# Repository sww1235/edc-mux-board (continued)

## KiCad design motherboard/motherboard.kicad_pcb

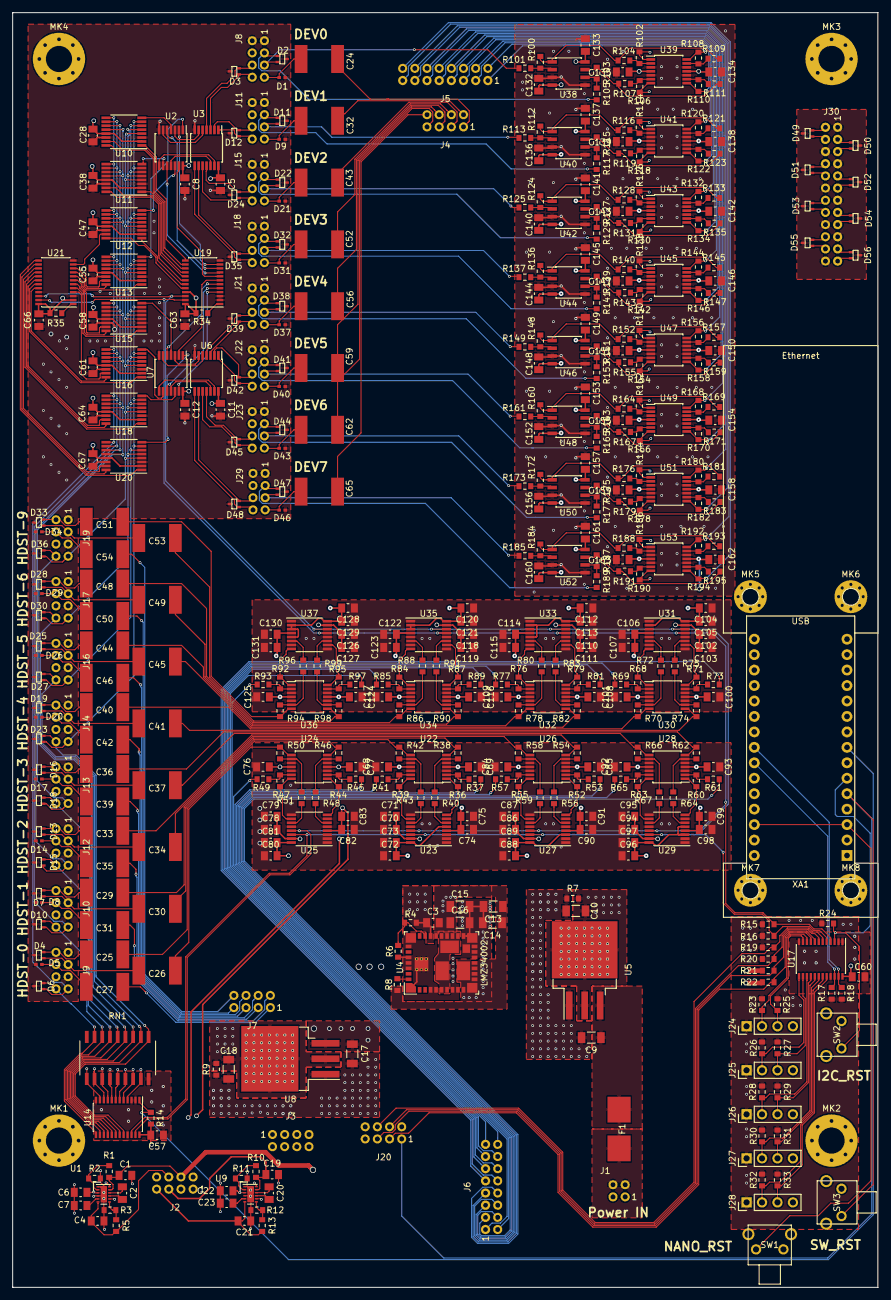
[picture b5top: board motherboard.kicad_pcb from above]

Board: 4 copper layers, 142.2 x 209.6 mm, 511 parts (0 on the bottom side), 384 nets.

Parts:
C1, C4, C19, C21: 2u2F; C_0805_2012Metric_Pad1.15x1.50mm_HandSolder
C2, C20: 0.47uF; C_0805_2012Metric_Pad1.15x1.50mm_HandSolder
C3: 15uF; C_0805_2012Metric_Pad1.15x1.50mm_HandSolder
C5, C8, C11, C12, C28, C38, C47, C55, C57, C58, C60, C61, C63, C64, C66, C67, C68, C69, C71, C72, C75, C76, C77, C79, C80, C83, C84, C85, C87, C88, C91, C92, C93, C95, C96, C99, C100, C101, C103, C104, C107, C108, C109, C111, C112, C115, C116, C117, C119, C120, C123, C124, C125, C127, C128, C131, C132, C133, C134, C135, C136, C137, C138, C139, C140, C141, C142, C143, C144, C145, C146, C147, C148, C149, C150, C151, C152, C153, C154, C155, C156, C157, C158, C159, C160, C161, C162, C163: 0.1uF; C_0805_2012Metric_Pad1.15x1.50mm_HandSolder
C6, C7, C22, C23: 4u7F; C_0805_2012Metric_Pad1.15x1.50mm_HandSolder
C9, C10, C17, C18: 10uF; C_1206_3216Metric_Pad1.24x1.80mm_HandSolder
C13, C14, C15, C16: 22uF; C_1206_3216Metric_Pad1.24x1.80mm_HandSolder
C24, C25, C26, C27, C29, C30, C31, C32, C33, C34, C35, C36, C37, C39, C40, C41, C42, C43, C44, C45, C46, C48, C49, C50, C51, C52, C53, C54, C56, C59, C62, C65: 1uF; Kemet_CAP_2220_5750Metric_D
C70, C73, C74, C78, C81, C82, C86, C89, C90, C94, C97, C98, C102, C105, C106, C110, C113, C114, C118, C121, C122, C126, C129, C130: 0.01uF; C_0805_2012Metric_Pad1.15x1.50mm_HandSolder
D1, D5, D8, D9, D14, D17, D20, D21, D26, D29, D31, D34, D37, D40, D43, D46: TPD1E10B06; DPY_(R-PX1SON-N2)
D2, D3, D4, D6, D7, D10, D11, D12, D13, D15, D16, D18, D19, D22, D23, D24, D25, D27, D28, D30, D32, D33, D35, D36, D38, D39, D41, D42, D44, D45, D47, D48, D49, D50, D51, D52, D53, D54, D55, D56: 0582BQ; SC-75_3L
F1: 5A; NANO-0154-OMNI-BLOK-Fuse-Holder
J1: Power In (Male-top); DF11-4DP-2DSA
J2: Power Out (Male-top); DF11-8DP-2DSA
J3: GND (Male-top); DF11-8DP-2DSA
J4: MIC-IN (Male-top); DF11-8DP-2DSA
J5: Headphone Audio Out (Male-top); DF11-16DP-2DSA
J6: Headphone Audio In (Male-top); DF11-16DP-2DSA
J7: MIC-OUT (Male-top); DF11-8DP-2DSA
J8: Device 0; DF11-8DP-2DSA
J9: Headset 0; DF11-8DP-2DSA
J10: Headset 1; DF11-8DP-2DSA
J11: Device 1; DF11-8DP-2DSA
J12: Headset 2; DF11-8DP-2DSA
J13: Headset 3; DF11-8DP-2DSA
J14: Headset 4; DF11-8DP-2DSA
J15: Device 2; DF11-8DP-2DSA
J16: Headset 5; DF11-8DP-2DSA
J17: Headset 6; DF11-8DP-2DSA
J18: Device 3; DF11-8DP-2DSA
J19: Headset 7; DF11-8DP-2DSA
J20: I2C and RESET (Male-top); DF11-8DP-2DSA
J21: Device 4; DF11-8DP-2DSA
J22: Device 5; DF11-8DP-2DSA
J23: Device 6; DF11-8DP-2DSA
J24: 5V-I2C-2; PinHeader_1x04_P2.54mm_Vertical
J25: 5V-I2C-3; PinHeader_1x04_P2.54mm_Vertical
J26: 5V-I2C-4; PinHeader_1x04_P2.54mm_Vertical
J27: 5V-I2C-5; PinHeader_1x04_P2.54mm_Vertical
J28: 5V-I2C-6; PinHeader_1x04_P2.54mm_Vertical
J29: Device 7; DF11-8DP-2DSA
J30: Output to Mixer; DF11-24DP-2DSA
MK1, MK2, MK3, MK4: Mounting_Hole_PAD; MountingHole_4.3mm_M4_Pad_Via
MK5, MK6, MK7, MK8: Mounting_Hole_PAD; MountingHole_2.7mm_M2.5_Pad_Via
R1, R5: 75kΩ; R_0603_1608Metric_Pad0.84x1.00mm_HandSolder
R2, R3, R11, R12: 68kΩ; R_0603_1608Metric_Pad0.84x1.00mm_HandSolder
R4: 174kΩ; R_0603_1608Metric_Pad0.84x1.00mm_HandSolder
R6: 22.6kΩ; R_0603_1608Metric_Pad0.84x1.00mm_HandSolder
R7, R9: 1.3Ω; R_0603_1608Metric_Pad0.84x1.00mm_HandSolder
R8: 143kΩ; R_0603_1608Metric_Pad0.84x1.00mm_HandSolder
R10, R13: 220kΩ; R_0603_1608Metric_Pad0.84x1.00mm_HandSolder
R14, R24, R34, R35, R40, R43, R48, R51, R56, R59, R64, R67, R72, R75, R80, R83, R88, R91, R96, R99: 10kΩ; R_0603_1608Metric_Pad0.84x1.00mm_HandSolder
R15, R16, R17, R18, R19, R20, R21, R22, R23, R25, R26, R27, R28, R29, R30, R31, R32, R33: 4k7Ω; R_0603_1608Metric_Pad0.84x1.00mm_HandSolder
R36, R37, R38, R39, R41, R42, R44, R45, R46, R47, R49, R50, R52, R53, R54, R55, R57, R58, R60, R61, R62, R63, R65, R66, R68, R69, R70, R71, R73, R74, R76, R77, R78, R79, R81, R82, R84, R85, R86, R87, R89, R90, R92, R93, R94, R95, R97, R98, R100, R101, R102, R103, R104, R105, R106, R107, R108, R109, R110, R111, R112, R113, R114, R115, R116, R117, R118, R119, R120, R121, R122, R123, R124, R125, R126, R127, R128, R129, R130, R131, R132, R133, R134, R135, R136, R137, R138, R139, R140, R141, R142, R143, R144, R145, R146, R147, R148, R149, R150, R151, R152, R153, R154, R155, R156, R157, R158, R159, R160, R161, R162, R163, R164, R165, R166, R167, R168, R169, R170, R171, R172, R173, R174, R175, R176, R177, R178, R179, R180, R181, R182, R183, R184, R185, R186, R187, R188, R189, R190, R191, R192, R193, R194, R195: 100kΩ; R_0603_1608Metric_Pad0.84x1.00mm_HandSolder
RN1: 4818P-T02-202LF; SOM-18
SW1: Nano Reset; TL1105WF
SW2: I2C Reset; TL1105WF
SW3: SPST Reset; TL1105WF
U1, U9: LM27762; WSON-12-1EP_3x2mm_P0.5mm
U2, U7: 74ACT32; TSSOP-14_4.4x5mm_P0.65mm
U3, U6: TS12A44514; TSSOP-14_4.4x5mm_P0.65mm
U4: LMZ34002; RKG_(S-PB1QFN-N41)
U5: LM1085-12V; TO-263-3_TabPin4
U8: LM1085-5V; TO-263-3_TabPin4
U10, U11, U12, U13, U15, U16, U18, U20: ADG708; TSSOP-16_4.4x5mm_P0.65mm
U14, U19, U21: TCA9555; TSSOP-24_4.4x7.8mm_P0.65mm
U17: TCA9548A; TSSOP-24_4.4x7.8mm_P0.65mm
U22, U24, U26, U28, U30, U32, U34, U36, U39, U41, U43, U45, U47, U49, U51, U53: OPA1604; TSSOP-14_4.4x5mm_P0.65mm
U23, U25, U27, U29, U31, U33, U35, U37: DS1882; TSSOP-16_4.4x5mm_P0.65mm
U38, U40, U42, U44, U46, U48, U50, U52: OPA1602; SOIC-8_3.9x4.9mm_P1.27mm
XA1: Nano_Headers; Nano-Header-Ethernet-4NANO

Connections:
+2V5: C1.1, J2.4, R1.1, R21.1, R22.1, U1.11
+3V3: C60.2, U17.24, XA1.17
+5V: C5.1, C6.1, C8.1, C11.1, C12.1, C18.1, C22.1, C28.1, C38.1, C47.1, C55.1, C57.2, C58.1, C61.1, C63.2, C64.1, C66.2, C67.1, C72.2, C73.2, C80.2, C81.2, C88.2, C89.2, C96.2, C97.2, C104.2, C105.2, C112.2, C113.2, C120.2, C121.2, C128.2, C129.2, J2.1, J8.4, J9.6, J10.6, J11.4, J12.6, J13.6, J14.6, J15.4, J16.6, J17.6, J18.4, J19.6, J21.4, J22.4, J23.4, J24.1, J25.1, J26.1, J27.1, J28.1, J29.4, R9.2, R14.1, R15.1, R16.1, R17.1, R18.1, R19.1, R20.1, R23.1, R24.1, R25.1, R26.1, R27.1, R28.1, R29.1, R30.1, R31.1, R32.1, R33.1, R34.1, R35.1, U1.3, U1.8, U1.12, U2.14, U3.14, U6.14, U7.14, U8.2, U8.4, U9.3, U9.8, U9.12, U10.2, U10.13, U11.2, U11.13, U12.2, U12.13, U13.2, U13.13, U14.24, U15.2, U15.13, U16.2, U16.13, U18.2, U18.13, U19.21, U19.24, U20.2, U20.13, U21.2, U21.24, U23.5, U23.16, U25.16, U27.3, U27.16, U29.3, U29.5, U29.16, U31.2, U31.16, U33.2, U33.5, U33.16, U35.2, U35.3, U35.16, U37.2, U37.3, U37.5, U37.16, XA1.27
+5VA: C19.1, C70.2, C71.2, C78.2, C79.2, C86.2, C87.2, C94.2, C95.2, C102.2, C103.2, C110.2, C111.2, C118.2, C119.2, C126.2, C127.2, J2.5, R10.1, U9.11, U23.15, U25.15, U27.15, U29.15, U31.15, U33.15, U35.15, U37.15
+12V: C3.1, C10.1, C17.1, C69.2, C77.2, C85.2, C93.2, C101.2, C109.2, C117.2, C125.2, C133.2, C135.2, C137.2, C139.2, C141.2, C143.2, C145.2, C147.2, C149.2, C151.2, C153.2, C155.2, C157.2, C159.2, C161.2, C163.2, J2.2, R4.1, R7.2, U4.26, U5.2, U5.4, U8.3, U22.4, U24.4, U26.4, U28.4, U30.4, U32.4, U34.4, U36.4, U38.8, U39.4, U40.8, U41.4, U42.8, U43.4, U44.8, U45.4, U46.8, U47.4, U48.8, U49.4, U50.8, U51.4, U52.8, U53.4
-2.5V: C4.2, J2.6, R5.2, U1.6
-5VA: C21.2, C74.2, C75.2, C82.2, C83.2, C90.2, C91.2, C98.2, C99.2, C106.2, C107.2, C114.2, C115.2, C122.2, C123.2, C130.2, C131.2, J2.7, R13.2, U9.6, U23.4, U25.4, U27.4, U29.4, U31.4, U33.4, U35.4, U37.4
-12VA: C13.2, C14.2, C15.2, C16.2, C68.2, C76.2, C84.2, C92.2, C100.2, C108.2, C116.2, C124.2, C132.2, C134.2, C136.2, C138.2, C140.2, C142.2, C144.2, C146.2, C148.2, C150.2, C152.2, C154.2, C156.2, C158.2, C160.2, C162.2, J2.8, R6.2, U4.1, U4.4, U4.5, U4.8, U4.9, U4.16, U4.17, U4.18, U4.19, U4.20, U4.29, U4.30, U4.32, U4.33, U4.34, U4.37, U4.40, U22.11, U24.11, U26.11, U28.11, U30.11, U32.11, U34.11, U36.11, U38.4, U39.11, U40.4, U41.11, U42.4, U43.11, U44.4, U45.11, U46.4, U47.11, U48.4, U49.11, U50.4, U51.11, U52.4, U53.11
/Arduino Nano Header Connections + Ethernet connection/5V-SCL: R17.2, U17.22, XA1.24
/Arduino Nano Header Connections + Ethernet connection/5V-SDA: R18.2, U17.23, XA1.23
/Arduino Nano Header Connections + Ethernet connection/D2_SPST: J20.1, SW3.1, XA1.5
/Arduino Nano Header Connections + Ethernet connection/D3_I2C: R24.2, SW2.1, U17.3, XA1.6
/Arduino Nano Header Connections + Ethernet connection/D5_INT: R14.2, U14.1, XA1.8
/Arduino Nano Header Connections + Ethernet connection/Nano_RST: SW1.1, XA1.3, XA1.28
/Audio Mux and Control/2v5-SCL-0: J20.3, R22.2, U17.9
/Audio Mux and Control/2v5-SDA-0: J20.5, R21.2, U17.8
/Audio Mux and Control/5V-SCL-0: R16.2, U14.22, U17.5, U19.22, U21.22, U23.14, U25.14, U27.14, U29.14, U31.14, U33.14, U35.14, U37.14
/Audio Mux and Control/5V-SCL-1: J20.4, R20.2, U17.7
/Audio Mux and Control/5V-SCL-2: J24.3, R25.2, U17.11
/Audio Mux and Control/5V-SCL-3: J25.3, R27.2, U17.14
/Audio Mux and Control/5V-SCL-4: J26.3, R29.2, U17.16
/Audio Mux and Control/5V-SCL-5: J27.3, R31.2, U17.18
/Audio Mux and Control/5V-SCL-6: J28.3, R33.2, U17.20
/Audio Mux and Control/5V-SDA-0: R15.2, U14.23, U17.4, U19.23, U21.23, U23.13, U25.13, U27.13, U29.13, U31.13, U33.13, U35.13, U37.13
/Audio Mux and Control/5V-SDA-1: J20.6, R19.2, U17.6
/Audio Mux and Control/5V-SDA-2: J24.2, R23.2, U17.10
/Audio Mux and Control/5V-SDA-3: J25.2, R26.2, U17.13
/Audio Mux and Control/5V-SDA-4: J26.2, R28.2, U17.15
/Audio Mux and Control/5V-SDA-5: J27.2, R30.2, U17.17
/Audio Mux and Control/5V-SDA-6: J28.2, R32.2, U17.19
/Audio Mux and Control/DEV-PTT-TRGR-0: U2.6, U3.5
/Audio Mux and Control/DEV-PTT-TRGR-1: U2.8, U3.13
/Audio Mux and Control/DEV-PTT-TRGR-2: U2.11, U3.12
/Audio Mux and Control/DEV-PTT-TRGR-3: U2.3, U3.6
/Audio Mux and Control/DEV-PTT-TRGR-4: U6.5, U7.6
/Audio Mux and Control/DEV-PTT-TRGR-5: U6.13, U7.8
/Audio Mux and Control/DEV-PTT-TRGR-6: U6.12, U7.11
/Audio Mux and Control/DEV-PTT-TRGR-7: U6.6, U7.3
/Audio Mux and Control/DEV-PTT-XBAR-CTL0: U10.1, U19.13
/Audio Mux and Control/DEV-PTT-XBAR-CTL1: U10.16, U19.15
/Audio Mux and Control/DEV-PTT-XBAR-CTL2: U10.15, U19.14
/Audio Mux and Control/DEV-PTT-XBAR-CTL3: U11.1, U19.16
/Audio Mux and Control/DEV-PTT-XBAR-CTL4: U11.16, U19.18
/Audio Mux and Control/DEV-PTT-XBAR-CTL5: U11.15, U19.17
/Audio Mux and Control/DEV-PTT-XBAR-CTL6: U12.1, U19.19
/Audio Mux and Control/DEV-PTT-XBAR-CTL7: U12.16, U19.20
/Audio Mux and Control/DEV-PTT-XBAR-CTL8: U12.15, U21.11
/Audio Mux and Control/DEV-PTT-XBAR-CTL9: U13.1, U21.8
/Audio Mux and Control/DEV-PTT-XBAR-CTL10: U13.16, U21.9
/Audio Mux and Control/DEV-PTT-XBAR-CTL11: U13.15, U21.10
/Audio Mux and Control/DEV-PTT-XBAR-CTL12: U15.1, U21.5
/Audio Mux and Control/DEV-PTT-XBAR-CTL13: U15.16, U21.6
/Audio Mux and Control/DEV-PTT-XBAR-CTL14: U15.15, U21.7
/Audio Mux and Control/DEV-PTT-XBAR-CTL15: U16.1, U21.19
/Audio Mux and Control/DEV-PTT-XBAR-CTL16: U16.16, U21.20
/Audio Mux and Control/DEV-PTT-XBAR-CTL17: U16.15, U21.4
/Audio Mux and Control/DEV-PTT-XBAR-CTL18: U18.1, U21.16
/Audio Mux and Control/DEV-PTT-XBAR-CTL19: U18.16, U21.17
/Audio Mux and Control/DEV-PTT-XBAR-CTL20: U18.15, U21.18
/Audio Mux and Control/DEV-PTT-XBAR-CTL21: U20.1, U21.13
/Audio Mux and Control/DEV-PTT-XBAR-CTL22: U20.16, U21.14
/Audio Mux and Control/DEV-PTT-XBAR-CTL23: U20.15, U21.15
/Audio Mux and Control/Device LR Distro Amplifier 0/L_IN: D2.2, J8.5, R101.2
/Audio Mux and Control/Device LR Distro Amplifier 0/R_IN: D2.1, J8.3, R105.2
/Audio Mux and Control/Device LR Distro Amplifier 1/L_IN: D11.2, J11.5, R113.2
/Audio Mux and Control/Device LR Distro Amplifier 1/R_IN: D11.1, J11.3, R117.2
/Audio Mux and Control/Device LR Distro Amplifier 2/L_IN: D22.2, J15.5, R125.2
/Audio Mux and Control/Device LR Distro Amplifier 2/R_IN: D22.1, J15.3, R129.2
/Audio Mux and Control/Device LR Distro Amplifier 3/L_IN: D32.2, J18.5, R137.2
/Audio Mux and Control/Device LR Distro Amplifier 3/R_IN: D32.1, J18.3, R141.2
/Audio Mux and Control/Device LR Distro Amplifier 4/L_IN: D38.2, J21.5, R149.2
/Audio Mux and Control/Device LR Distro Amplifier 4/R_IN: D38.1, J21.3, R153.2
/Audio Mux and Control/Device LR Distro Amplifier 5/L_IN: D41.2, J22.5, R161.2
/Audio Mux and Control/Device LR Distro Amplifier 5/R_IN: D41.1, J22.3, R165.2
/Audio Mux and Control/Device LR Distro Amplifier 6/L_IN: D44.2, J23.5, R173.2
/Audio Mux and Control/Device LR Distro Amplifier 6/R_IN: D44.1, J23.3, R177.2
/Audio Mux and Control/Device LR Distro Amplifier 7/L_IN: D47.2, J29.5, R185.2
/Audio Mux and Control/Device LR Distro Amplifier 7/R_IN: D47.1, J29.3, R189.2
/Audio Mux and Control/HEADSET-AUDIO-SOURCE-L-0: J5.1, R108.1, U39.14
/Audio Mux and Control/HEADSET-AUDIO-SOURCE-L-1: J5.3, R120.1, U41.14
/Audio Mux and Control/HEADSET-AUDIO-SOURCE-L-2: J5.5, R132.1, U43.14
/Audio Mux and Control/HEADSET-AUDIO-SOURCE-L-3: J5.7, R144.1, U45.14
/Audio Mux and Control/HEADSET-AUDIO-SOURCE-L-4: J5.9, R156.1, U47.14
/Audio Mux and Control/HEADSET-AUDIO-SOURCE-L-5: J5.11, R168.1, U49.14
/Audio Mux and Control/HEADSET-AUDIO-SOURCE-L-6: J5.13, R180.1, U51.14
/Audio Mux and Control/HEADSET-AUDIO-SOURCE-L-7: J5.15, R192.1, U53.14
/Audio Mux and Control/HEADSET-AUDIO-SOURCE-R-0: J5.2, R110.1, U39.8
/Audio Mux and Control/HEADSET-AUDIO-SOURCE-R-1: J5.4, R122.1, U41.8
/Audio Mux and Control/HEADSET-AUDIO-SOURCE-R-2: J5.6, R134.1, U43.8
/Audio Mux and Control/HEADSET-AUDIO-SOURCE-R-3: J5.8, R146.1, U45.8
/Audio Mux and Control/HEADSET-AUDIO-SOURCE-R-4: J5.10, R158.1, U47.8
/Audio Mux and Control/HEADSET-AUDIO-SOURCE-R-5: J5.12, R170.1, U49.8
/Audio Mux and Control/HEADSET-AUDIO-SOURCE-R-6: J5.14, R182.1, U51.8
/Audio Mux and Control/HEADSET-AUDIO-SOURCE-R-7: J5.16, R194.1, U53.8
/Audio Mux and Control/L_OUT0: J6.2, R45.2
/Audio Mux and Control/L_OUT1: J6.4, R37.2
/Audio Mux and Control/L_OUT2: J6.6, R53.2
/Audio Mux and Control/L_OUT3: J6.8, R61.2
/Audio Mux and Control/L_OUT4: J6.10, R69.2
/Audio Mux and Control/L_OUT5: J6.12, R77.2
/Audio Mux and Control/L_OUT6: J6.14, R85.2
/Audio Mux and Control/L_OUT7: J6.16, R93.2
/Audio Mux and Control/MIC-IN0: C27.2, J7.1
/Audio Mux and Control/MIC-IN1: C31.2, J7.2
/Audio Mux and Control/MIC-IN2: C35.2, J7.3
/Audio Mux and Control/MIC-IN3: C39.2, J7.4
/Audio Mux and Control/MIC-IN4: C42.2, J7.5
/Audio Mux and Control/MIC-IN5: C46.2, J7.6
/Audio Mux and Control/MIC-IN6: C50.2, J7.7
/Audio Mux and Control/MIC-IN7: C54.2, J7.8
/Audio Mux and Control/MIC-MUTE-0: D6.2, J9.8, RN1.8, U14.13
/Audio Mux and Control/MIC-MUTE-1: D10.2, J10.8, RN1.7, U14.14
/Audio Mux and Control/MIC-MUTE-2: D15.2, J12.8, RN1.6, U14.15
/Audio Mux and Control/MIC-MUTE-3: D18.2, J13.8, RN1.5, U14.16
/Audio Mux and Control/MIC-MUTE-4: D23.2, J14.8, RN1.1, U14.20
/Audio Mux and Control/MIC-MUTE-5: D27.2, J16.8, RN1.2, U14.19
/Audio Mux and Control/MIC-MUTE-6: D30.2, J17.8, RN1.3, U14.18
/Audio Mux and Control/MIC-MUTE-7: D36.2, J19.8, RN1.4, U14.17
/Audio Mux and Control/MIC-OUT0: C24.1, J4.1
/Audio Mux and Control/MIC-OUT1: C32.1, J4.2
/Audio Mux and Control/MIC-OUT2: C43.1, J4.3
/Audio Mux and Control/MIC-OUT3: C52.1, J4.4
/Audio Mux and Control/MIC-OUT4: C56.1, J4.5
/Audio Mux and Control/MIC-OUT5: C59.1, J4.6
/Audio Mux and Control/MIC-OUT6: C62.1, J4.7
/Audio Mux and Control/MIC-OUT7: C65.1, J4.8
/Audio Mux and Control/MIXER-OUT-L-0: D49.2, J30.2, R102.1, U39.1
/Audio Mux and Control/MIXER-OUT-L-1: D50.1, J30.3, R114.1, U41.1
/Audio Mux and Control/MIXER-OUT-L-2: D51.2, J30.8, R126.1, U43.1
/Audio Mux and Control/MIXER-OUT-L-3: D52.1, J30.9, R138.1, U45.1
/Audio Mux and Control/MIXER-OUT-L-4: D53.2, J30.14, R150.1, U47.1
/Audio Mux and Control/MIXER-OUT-L-5: D54.1, J30.15, R162.1, U49.1
/Audio Mux and Control/MIXER-OUT-L-6: D55.2, J30.20, R174.1, U51.1
/Audio Mux and Control/MIXER-OUT-L-7: D56.1, J30.21, R186.1, U53.1
/Audio Mux and Control/MIXER-OUT-R-0: D49.1, J30.4, R106.1, U39.7
/Audio Mux and Control/MIXER-OUT-R-1: D50.2, J30.5, R118.1, U41.7
/Audio Mux and Control/MIXER-OUT-R-2: D51.1, J30.10, R130.1, U43.7
/Audio Mux and Control/MIXER-OUT-R-3: D52.2, J30.11, R142.1, U45.7
/Audio Mux and Control/MIXER-OUT-R-4: D53.1, J30.16, R154.1, U47.7
/Audio Mux and Control/MIXER-OUT-R-5: D54.2, J30.17, R166.1, U49.7
/Audio Mux and Control/MIXER-OUT-R-6: D55.1, J30.22, R178.1, U51.7
/Audio Mux and Control/MIXER-OUT-R-7: D56.2, J30.23, R190.1, U53.7
/Audio Mux and Control/MUX->OR-0: U2.4, U10.8
/Audio Mux and Control/MUX->OR-1: U2.9, U11.8
/Audio Mux and Control/MUX->OR-2: U2.12, U12.8
/Audio Mux and Control/MUX->OR-3: U2.1, U13.8
/Audio Mux and Control/MUX->OR-4: U7.4, U15.8
/Audio Mux and Control/MUX->OR-5: U7.9, U16.8
/Audio Mux and Control/MUX->OR-6: U7.12, U18.8
/Audio Mux and Control/MUX->OR-7: U7.1, U20.8
/Audio Mux and Control/PTT+DEV0: D3.2, J8.6, U3.4
/Audio Mux and Control/PTT+DEV1: D12.2, J11.6, U3.2
/Audio Mux and Control/PTT+DEV2: D24.2, J15.6, U3.11
/Audio Mux and Control/PTT+DEV3: D35.2, J18.6, U3.9
/Audio Mux and Control/PTT+DEV4: D39.2, J21.6, U6.4
/Audio Mux and Control/PTT+DEV5: D42.2, J22.6, U6.2
/Audio Mux and Control/PTT+DEV6: D45.2, J23.6, U6.11
/Audio Mux and Control/PTT+DEV7: D48.2, J29.6, U6.9
/Audio Mux and Control/PTT-0: D6.1, J9.7, RN1.10, U10.9, U11.9, U12.9, U13.9, U14.11, U15.9, U16.9, U18.9, U20.9
/Audio Mux and Control/PTT-1: D10.1, J10.7, RN1.11, U10.10, U11.10, U12.10, U13.10, U14.10, U15.10, U16.10, U18.10, U20.10
/Audio Mux and Control/PTT-2: D15.1, J12.7, RN1.12, U10.11, U11.11, U12.11, U13.11, U14.9, U15.11, U16.11, U18.11, U20.11
/Audio Mux and Control/PTT-3: D18.1, J13.7, RN1.13, U10.12, U11.12, U12.12, U13.12, U14.8, U15.12, U16.12, U18.12, U20.12
/Audio Mux and Control/PTT-4: D23.1, J14.7, RN1.14, U10.7, U11.7, U12.7, U13.7, U14.7, U15.7, U16.7, U18.7, U20.7
/Audio Mux and Control/PTT-5: D27.1, J16.7, RN1.15, U10.6, U11.6, U12.6, U13.6, U14.6, U15.6, U16.6, U18.6, U20.6
/Audio Mux and Control/PTT-6: D30.1, J17.7, RN1.16, U10.5, U11.5, U12.5, U13.5, U14.5, U15.5, U16.5, U18.5, U20.5
/Audio Mux and Control/PTT-7: D36.1, J19.7, RN1.17, U10.4, U11.4, U12.4, U13.4, U14.4, U15.4, U16.4, U18.4, U20.4
/Audio Mux and Control/PTT-DEV0: D3.1, J8.8, U3.3
/Audio Mux and Control/PTT-DEV1: D12.1, J11.8, U3.1
/Audio Mux and Control/PTT-DEV2: D24.1, J15.8, U3.10
/Audio Mux and Control/PTT-DEV3: D35.1, J18.8, U3.8
/Audio Mux and Control/PTT-DEV4: D39.1, J21.8, U6.3
/Audio Mux and Control/PTT-DEV5: D42.1, J22.8, U6.1
/Audio Mux and Control/PTT-DEV6: D45.1, J23.8, U6.10
/Audio Mux and Control/PTT-DEV7: D48.1, J29.8, U6.8
/Audio Mux and Control/RPI-PTT-0: U2.5, U19.10
/Audio Mux and Control/RPI-PTT-1: U2.10, U19.9
/Audio Mux and Control/RPI-PTT-2: U2.13, U19.8
/Audio Mux and Control/RPI-PTT-3: U2.2, U19.11
/Audio Mux and Control/RPI-PTT-4: U7.5, U19.6
/Audio Mux and Control/RPI-PTT-5: U7.10, U19.5
/Audio Mux and Control/RPI-PTT-6: U7.13, U19.4
/Audio Mux and Control/RPI-PTT-7: U7.2, U19.7
/Audio Mux and Control/R_OUT0: J6.1, R49.2
/Audio Mux and Control/R_OUT1: J6.3, R41.2
/Audio Mux and Control/R_OUT2: J6.5, R57.2
/Audio Mux and Control/R_OUT3: J6.7, R65.2
/Audio Mux and Control/R_OUT4: J6.9, R73.2
/Audio Mux and Control/R_OUT5: J6.11, R81.2
/Audio Mux and Control/R_OUT6: J6.13, R89.2
/Audio Mux and Control/R_OUT7: J6.15, R97.2
/Audio Mux and Control/Stereo Amplifier 0/L_OUT: C25.2, R46.1, U24.7
/Audio Mux and Control/Stereo Amplifier 0/R_OUT: C26.2, R50.1, U24.8
/Audio Mux and Control/Stereo Amplifier 1/L_OUT: C29.2, R38.1, U22.7
/Audio Mux and Control/Stereo Amplifier 1/R_OUT: C30.2, R42.1, U22.8
/Audio Mux and Control/Stereo Amplifier 2/L_OUT: C33.2, R54.1, U26.7
/Audio Mux and Control/Stereo Amplifier 2/R_OUT: C34.2, R58.1, U26.8
/Audio Mux and Control/Stereo Amplifier 3/L_OUT: C36.2, R62.1, U28.7
/Audio Mux and Control/Stereo Amplifier 3/R_OUT: C37.2, R66.1, U28.8
/Audio Mux and Control/Stereo Amplifier 4/L_OUT: C40.2, R70.1, U30.7
/Audio Mux and Control/Stereo Amplifier 4/R_OUT: C41.2, R74.1, U30.8
/Audio Mux and Control/Stereo Amplifier 5/L_OUT: C44.2, R78.1, U32.7
/Audio Mux and Control/Stereo Amplifier 5/R_OUT: C45.2, R82.1, U32.8
/Audio Mux and Control/Stereo Amplifier 6/L_OUT: C48.2, R86.1, U34.7
/Audio Mux and Control/Stereo Amplifier 6/R_OUT: C49.2, R90.1, U34.8
/Audio Mux and Control/Stereo Amplifier 7/L_OUT: C51.2, R94.1, U36.7
/Audio Mux and Control/Stereo Amplifier 7/R_OUT: C53.2, R98.1, U36.8
/Power Handling/+12V-F: C9.1, F1.2, U5.3
/Power Handling/VIN+: F1.1, J1.2, J1.4
GNDREF: C1.2, C3.2, C4.1, C5.2, C6.2, C7.2, C8.2, C9.2, C10.2, C11.2, C12.2, C13.1, C14.1, C15.1, C16.1, C17.2, C18.2, C19.2, C21.1, C22.2, C23.2, C28.2, C38.2, C47.2, C55.2, C57.1, C58.2, C60.1, C61.2, C63.1, C64.2, C66.1, C67.2, C68.1, C69.1, C70.1, C71.1, C72.1, C73.1, C74.1, C75.1, C76.1, C77.1, C78.1, C79.1, C80.1, C81.1, C82.1, C83.1, C84.1, C85.1, C86.1, C87.1, C88.1, C89.1, C90.1, C91.1, C92.1, C93.1, C94.1, C95.1, C96.1, C97.1, C98.1, C99.1, C100.1, C101.1, C102.1, C103.1, C104.1, C105.1, C106.1, C107.1, C108.1, C109.1, C110.1, C111.1, C112.1, C113.1, C114.1, C115.1, C116.1, C117.1, C118.1, C119.1, C120.1, C121.1, C122.1, C123.1, C124.1, C125.1, C126.1, C127.1, C128.1, C129.1, C130.1, C131.1, C132.1, C133.1, C134.1, C135.1, C136.1, C137.1, C138.1, C139.1, C140.1, C141.1, C142.1, C143.1, C144.1, C145.1, C146.1, C147.1, C148.1, C149.1, C150.1, C151.1, C152.1, C153.1, C154.1, C155.1, C156.1, C157.1, C158.1, C159.1, C160.1, C161.1, C162.1, C163.1, D1.2, D2.3, D3.3, D4.3, D5.1, D6.3, D7.3, D8.1, D9.2, D10.3, D11.3, D12.3, D13.3, D14.1, D15.3, D16.3, D17.1, D18.3, D19.3, D20.1, D21.2, D22.3, D23.3, D24.3, D25.3, D26.1, D27.3, D28.3, D29.1, D30.3, D31.2, D32.3, D33.3, D34.1, D35.3, D36.3, D37.2, D38.3, D39.3, D40.2, D41.3, D42.3, D43.2, D44.3, D45.3, D46.2, D47.3, D48.3, D49.3, D50.3, D51.3, D52.3, D53.3, D54.3, D55.3, D56.3, J1.1, J1.3, J2.3, J3.1, J3.2, J3.3, J3.4, J3.5, J3.6, J3.7, J3.8, J8.1, J8.2, J9.1, J9.5, J10.1, J10.5, J11.1, J11.2, J12.1, J12.5, J13.1, J13.5, J14.1, J14.5, J15.1, J15.2, J16.1, J16.5, J17.1, J17.5, J18.1, J18.2, J19.1, J19.5, J20.2, J20.7, J20.8, J21.1, J21.2, J22.1, J22.2, J23.1, J23.2, J24.4, J25.4, J26.4, J27.4, J28.4, J29.1, J29.2, J30.1, J30.6, J30.7, J30.12, J30.13, J30.18, J30.19, J30.24, MK1.1, MK2.1, MK3.1, MK4.1, MK5.1, MK6.1, MK7.1, MK8.1, R2.2, R3.1, R7.1, R8.2, R9.1, R11.2, R12.1, RN1.18, SW1.0, SW1.2, SW2.0, SW2.2, SW3.0, SW3.2, U1.1, U1.4, U1.13, U2.7, U3.7, U4.10, U4.11, U4.12, U4.13, U4.14, U4.15, U4.39, U5.1, U6.7, U7.7, U8.1, U9.1, U9.4, U9.13, U10.3, U10.14, U11.3, U11.14, U12.3, U12.14, U13.3, U13.14, U14.2, U14.3, U14.12, U14.21, U15.3, U15.14, U16.3, U16.14, U17.1, U17.2, U17.12, U17.21, U18.3, U18.14, U19.2, U19.3, U19.12, U20.3, U20.14, U21.3, U21.12, U21.21, U22.3, U22.5, U22.10, U22.12, U23.1, U23.2, U23.3, U23.7, U23.9, U23.12, U24.3, U24.5, U24.10, U24.12, U25.1, U25.2, U25.3, U25.5, U25.7, U25.9, U25.12, U26.3, U26.5, U26.10, U26.12, U27.1, U27.2, U27.5, U27.7, U27.9, U27.12, U28.3, U28.5, U28.10, U28.12, U29.1, U29.2, U29.7, U29.9, U29.12, U30.3, U30.5, U30.10, U30.12, U31.1, U31.3, U31.5, U31.7, U31.9, U31.12, U32.3, U32.5, U32.10, U32.12, U33.1, U33.3, U33.7, U33.9, U33.12, U34.3, U34.5, U34.10, U34.12, U35.1, U35.5, U35.7, U35.9, U35.12, U36.3, U36.5, U36.10, U36.12, U37.1, U37.7, U37.9, U37.12, U38.3, U38.5, U39.3, U39.5, U39.10, U39.12, U40.3, U40.5, U41.3, U41.5, U41.10, U41.12, U42.3, U42.5, U43.3, U43.5, U43.10, U43.12, U44.3, U44.5, U45.3, U45.5, U45.10, U45.12, U46.3, U46.5, U47.3, U47.5, U47.10, U47.12, U48.3, U48.5, U49.3, U49.5, U49.10, U49.12, U50.3, U50.5, U51.3, U51.5, U51.10, U51.12, U52.3, U52.5, U53.3, U53.5, U53.10, U53.12, XA1.4, XA1.29
unnamed: C2.1, U1.10
unnamed: C2.2, U1.9
unnamed: C7.1, U1.5
unnamed: C20.1, U9.10
unnamed: C20.2, U9.9
unnamed: C23.1, U9.5
unnamed: C24.2, D1.1, J8.7
unnamed: C25.1, D4.2, J9.2
unnamed: C26.1, D4.1, J9.3
unnamed: C27.1, D5.2, J9.4
unnamed: C29.1, D7.2, J10.2
unnamed: C30.1, D7.1, J10.3
unnamed: C31.1, D8.2, J10.4
unnamed: C32.2, D9.1, J11.7
unnamed: C33.1, D13.2, J12.2
unnamed: C34.1, D13.1, J12.3
unnamed: C35.1, D14.2, J12.4
unnamed: C36.1, D16.2, J13.2
unnamed: C37.1, D16.1, J13.3
unnamed: C39.1, D17.2, J13.4
unnamed: C40.1, D19.2, J14.2
unnamed: C41.1, D19.1, J14.3
unnamed: C42.1, D20.2, J14.4
unnamed: C43.2, D21.1, J15.7
unnamed: C44.1, D25.2, J16.2
unnamed: C45.1, D25.1, J16.3
unnamed: C46.1, D26.2, J16.4
unnamed: C48.1, D28.2, J17.2
unnamed: C49.1, D28.1, J17.3
unnamed: C50.1, D29.2, J17.4
unnamed: C51.1, D33.2, J19.2
unnamed: C52.2, D31.1, J18.7
unnamed: C53.1, D33.1, J19.3
unnamed: C54.1, D34.2, J19.4
unnamed: C56.2, D37.1, J21.7
unnamed: C59.2, D40.1, J22.7
unnamed: C62.2, D43.1, J23.7
unnamed: C65.2, D46.1, J29.7
unnamed: R1.2, R2.1, U1.2
unnamed: R3.2, R5.1, U1.7
unnamed: R4.2, R6.1, U4.27
unnamed: R8.1, U4.36
unnamed: R10.2, R11.1, U9.2
unnamed: R12.2, R13.1, U9.7
unnamed: R34.2, U19.1
unnamed: R35.2, U21.1
unnamed: R36.1, U22.1, U23.8
unnamed: R36.2, R37.1, U22.2
unnamed: R38.2, R40.1, U22.6
unnamed: R39.1, U22.14, U23.10
unnamed: R39.2, R41.1, U22.13
unnamed: R40.2, U23.6
unnamed: R42.2, R43.1, U22.9
unnamed: R43.2, U23.11
unnamed: R44.1, U24.1, U25.8
unnamed: R44.2, R45.1, U24.2
unnamed: R46.2, R48.1, U24.6
unnamed: R47.1, U24.14, U25.10
unnamed: R47.2, R49.1, U24.13
unnamed: R48.2, U25.6
unnamed: R50.2, R51.1, U24.9
unnamed: R51.2, U25.11
unnamed: R52.1, U26.1, U27.8
unnamed: R52.2, R53.1, U26.2
unnamed: R54.2, R56.1, U26.6
unnamed: R55.1, U26.14, U27.10
unnamed: R55.2, R57.1, U26.13
unnamed: R56.2, U27.6
unnamed: R58.2, R59.1, U26.9
unnamed: R59.2, U27.11
unnamed: R60.1, U28.1, U29.8
unnamed: R60.2, R61.1, U28.2
unnamed: R62.2, R64.1, U28.6
unnamed: R63.1, U28.14, U29.10
unnamed: R63.2, R65.1, U28.13
unnamed: R64.2, U29.6
unnamed: R66.2, R67.1, U28.9
unnamed: R67.2, U29.11
unnamed: R68.1, U30.1, U31.8
unnamed: R68.2, R69.1, U30.2
unnamed: R70.2, R72.1, U30.6
unnamed: R71.1, U30.14, U31.10
unnamed: R71.2, R73.1, U30.13
unnamed: R72.2, U31.6
unnamed: R74.2, R75.1, U30.9
unnamed: R75.2, U31.11
unnamed: R76.1, U32.1, U33.8
unnamed: R76.2, R77.1, U32.2
unnamed: R78.2, R80.1, U32.6
unnamed: R79.1, U32.14, U33.10
unnamed: R79.2, R81.1, U32.13
unnamed: R80.2, U33.6
unnamed: R82.2, R83.1, U32.9
unnamed: R83.2, U33.11
unnamed: R84.1, U34.1, U35.8
unnamed: R84.2, R85.1, U34.2
unnamed: R86.2, R88.1, U34.6
unnamed: R87.1, U34.14, U35.10
unnamed: R87.2, R89.1, U34.13
unnamed: R88.2, U35.6
unnamed: R90.2, R91.1, U34.9
unnamed: R91.2, U35.11
unnamed: R92.1, U36.1, U37.8
unnamed: R92.2, R93.1, U36.2
unnamed: R94.2, R96.1, U36.6
unnamed: R95.1, U36.14, U37.10
unnamed: R95.2, R97.1, U36.13
unnamed: R96.2, U37.6
unnamed: R98.2, R99.1, U36.9
unnamed: R99.2, U37.11
unnamed: R100.1, R104.2, R109.2, U38.1
unnamed: R100.2, R101.1, U38.2
unnamed: R102.2, R104.1, U39.2
unnamed: R103.1, R107.2, R111.2, U38.7
unnamed: R103.2, R105.1, U38.6
unnamed: R106.2, R107.1, U39.6
unnamed: R108.2, R109.1, U39.13
unnamed: R110.2, R111.1, U39.9
unnamed: R112.1, R116.2, R121.2, U40.1
unnamed: R112.2, R113.1, U40.2
unnamed: R114.2, R116.1, U41.2
unnamed: R115.1, R119.2, R123.2, U40.7
unnamed: R115.2, R117.1, U40.6
unnamed: R118.2, R119.1, U41.6
unnamed: R120.2, R121.1, U41.13
unnamed: R122.2, R123.1, U41.9
unnamed: R124.1, R128.2, R133.2, U42.1
unnamed: R124.2, R125.1, U42.2
unnamed: R126.2, R128.1, U43.2
unnamed: R127.1, R131.2, R135.2, U42.7
unnamed: R127.2, R129.1, U42.6
unnamed: R130.2, R131.1, U43.6
unnamed: R132.2, R133.1, U43.13
unnamed: R134.2, R135.1, U43.9
unnamed: R136.1, R140.2, R145.2, U44.1
unnamed: R136.2, R137.1, U44.2
unnamed: R138.2, R140.1, U45.2
unnamed: R139.1, R143.2, R147.2, U44.7
unnamed: R139.2, R141.1, U44.6
unnamed: R142.2, R143.1, U45.6
unnamed: R144.2, R145.1, U45.13
unnamed: R146.2, R147.1, U45.9
unnamed: R148.1, R152.2, R157.2, U46.1
unnamed: R148.2, R149.1, U46.2
unnamed: R150.2, R152.1, U47.2
unnamed: R151.1, R155.2, R159.2, U46.7
unnamed: R151.2, R153.1, U46.6
unnamed: R154.2, R155.1, U47.6
unnamed: R156.2, R157.1, U47.13
unnamed: R158.2, R159.1, U47.9
unnamed: R160.1, R164.2, R169.2, U48.1
unnamed: R160.2, R161.1, U48.2
unnamed: R162.2, R164.1, U49.2
unnamed: R163.1, R167.2, R171.2, U48.7
unnamed: R163.2, R165.1, U48.6
unnamed: R166.2, R167.1, U49.6
unnamed: R168.2, R169.1, U49.13
unnamed: R170.2, R171.1, U49.9
unnamed: R172.1, R176.2, R181.2, U50.1
unnamed: R172.2, R173.1, U50.2
unnamed: R174.2, R176.1, U51.2
unnamed: R175.1, R179.2, R183.2, U50.7
unnamed: R175.2, R177.1, U50.6
unnamed: R178.2, R179.1, U51.6
unnamed: R180.2, R181.1, U51.13
unnamed: R182.2, R183.1, U51.9
unnamed: R184.1, R188.2, R193.2, U52.1
unnamed: R184.2, R185.1, U52.2
unnamed: R186.2, R188.1, U53.2
unnamed: R187.1, R191.2, R195.2, U52.7
unnamed: R187.2, R189.1, U52.6
unnamed: R190.2, R191.1, U53.6
unnamed: R192.2, R193.1, U53.13
unnamed: R194.2, R195.1, U53.9
unnamed: U4.6, U4.7, U4.21, U4.22, U4.23, U4.24, U4.38, U4.41

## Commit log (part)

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2019-02-17 fixed index issue
2019-02-17 start fixing assignment loop
2019-02-18 changed comment after changing size of ctl type
2019-02-18 fixed combinational logic loops in mixer and moved to adder tree logic
2019-02-18 no newline at end of file
2019-02-18 fucking commas
2019-02-18 changing everything over to integers, and now hopefully things work
2019-02-18 fixed sensivity list of mixer process
2019-02-18 added SB_IO to see if tristate output will work
2019-02-18 updated more gitignores
2019-02-18 removed files
2019-02-18 add ice libraries
2019-02-18 split sda into separate IO lines
2019-02-18 remove more project files
2019-02-18 verified all resets are active high
2019-02-19 removed more files
2019-02-19 ignoring all implementation files
2019-02-19 more removals
2019-02-19 testing removal of library
2019-02-19 add external constraints file
2019-02-19 attempting to fix issues with i2c stuff
2019-02-22 ignored intel project files for now
2019-02-22 fixed max signed int range
2019-02-23 fixed comments
2019-02-23 added reference file
2019-02-23 added comment to reference file
2019-02-23 comments
2019-02-23 fixed sensitivity list
2019-02-23 fixed scl being inout. No clock stretching needed
2019-02-23 no blank line at eof
2019-02-23 fixed integer range
2019-02-24 reworked serial2parallel code
2019-02-24 removed extra '0's from integer casting
2019-02-24 fixing spacing
2019-02-25 switching architecture name
2019-02-25 pipelining fullmixer
    added state machine and new mixerchannel entity
2019-02-27 updated clock specification file
2019-02-28 added more clocks to sdc file
2019-02-28 slowed down output selection and made it fit better in timing
2019-02-28 forgot how to do assignments in VHDL. Should not be coding this late at night
2019-02-28 removed bad clock statement
2019-03-27 starting to add another mixer channel into the mix
2019-03-29 Revert "more work on dual channel version"
    This reverts commit d0fb8f6a17f0024daa39a59b9e73851b243f9f30.
2019-03-29 Revert "starting to add another mixer channel into the mix"
    This reverts commit 949e16834cb3b83332b6544d9c3cc906b24c9c3a.
2019-03-29 more logic reorg
2019-04-05 changing to TLV320AIC3206 due to lower power consumption
2019-04-05 starting new pcb design
2019-04-05 more changes
2019-04-07 more updates to design notes
2019-04-07 MEMS Oscillator swap to newer version
2019-04-07 Added more sheets
2019-04-07 something changed?
2019-04-07 added more parts
2019-04-07 added subsheets
2019-04-07 started ethernet schematic
2019-04-08 fixed missing cache library in sheets
2019-04-08 initial round of design on clock sheet done
2019-04-08 sheets never got added?
2019-04-08 started working on PCB layout
2019-04-08 changed clock generator
2019-04-09 changed order of pins on connector
2019-04-09 device and headset interface boards notes
2019-04-09 added more libraries
2019-04-09 added 2 i2c muxes
2019-04-09 mostly finished one connector interface sheet. Ready to copy over to others and import sheet pins
2019-04-09 added P82B96 i2c bidirectional buffer to implementation notes
2019-04-09 renamed connector
2019-04-09 Reorganized connector interface subsheets
2019-04-10 added footprints, removed annotation
2019-04-10 changed footprint for device connector header
2019-04-10 updated board
2019-04-10 moved testbench file
2019-04-10 changed from film to ceramic 1uF caps and updated fields of other caps
2019-04-12 changed shotkey diode to mosfet + controller
2019-04-12 power and initial connections for microprocessor
2019-04-12 added new sheet
2019-04-12 fixed sheet pin positioning
2019-04-12 flipping half the sheets
2019-04-12 flipping ID pins
2019-04-12 added interrupt pin to connector pinout
2019-04-12 moving FPGA interconnections to root sheet.
2019-04-13 ignored modelsim specific simulation output files
2019-04-13 Copied over conn-0 changes to other conn sheets
    Removing IO connectors from sheet
2019-04-13 sheet number changed
2019-04-14 for some reason the orientation matricies keep changing.
    Not sure if this is a KiCAD or windows issue
2019-04-14 Added ground pin to connector, and changed power inptu connector
2019-04-14 Finished Codec Interconnect Busses
2019-04-14 connected up mclks for codecs
2019-04-15 Finished CODEC and MCU interconnections
2019-04-15 changed ID requirements for bus
2019-04-15 assigning default value to data_to_master
2019-04-15 Added pin assignment report from quartus prime
2019-04-16 Finished FPGA and MCU interconnections.
    Finished up interrupt wiring
    Fixed a few missing connections
    Annotated Schematic
2019-04-16 adding power report from output files
2019-04-18 fixed USB connector by using my own *sane* libraries
2019-04-18 Add switchcraft footprint library
2019-04-19 starting work on power supply
2019-04-20 starting interface board template
2019-04-20 Moved all lower voltages to be powered off of 3v3 rail
2019-04-21 Finished off power supplies and decoupling capacitors.
    Decoupling calculations for the FPGA are found in
    ../fpga-decoupling-calculations
2019-04-22 removed polyfuses
    at the right rating they were going to be too big.
2019-04-22 Adding reverse voltage protection to DC input
2019-04-22 Fixed pin header footprint issues
2019-04-28 updated power usage table
2019-04-28 Added labels to nets
2019-04-28 corrected the fact that input and output busses were swapped
2019-04-28 Changed capacitor orientation
2019-04-28 fixed swapped bus labels
2019-04-28 ignored log files
2019-04-28 Added pcb design rules
2019-05-04 updating sdc file
2019-05-04 adding comments
2019-05-04 updating FPGA pin assignments in schematic
2019-05-04 removing old symbols
2019-05-04 switched to using one back end file for all conn* schematic sheets.
    Since they were identical anyways and the connectors that needed
    different names are in different sheets.
2019-05-05 Reannotating board
2019-05-05 more pcb work
    all codecs laid out
    left side daughterboard laid out
    started working on slots to separate daughterboard
2019-05-06 switching sheet paper sizes
2019-05-06 Adding wire labels
2019-05-06 moving main 12V regulator to bottom daughterboard
2019-05-06 pcb changes from moving 12v regulator
2019-05-07 better laid out bottom connector daughterboard
2019-05-07 of course the darn subsheet units keep changing
2019-05-07 modified external connector pinout to match up better with mezzanine connector pinout and circular connector layout
2019-05-07 starting layout again
2019-05-07 swapping sda and scl pins
2019-05-07 a bit more pcb cleanup before bed
2019-05-14 fixed IO conn pinouts and mezz board pinouts on bottom and right mezz boards
2019-05-14 fixed i2c pinouts on bottom and right mezz connectors
2019-05-14 changed pinout on IO connectors again
2019-05-14 Finished routing all mezzanine boards
2019-05-14 moved around mclk connections on clock distribution to make routing easier
2019-05-15 Flipped 12V regulator to back of mezzanine board
2019-05-15 Swapping pins on clock distro 2
2019-05-15 Changed out top conn mezz header schematic symbol to make more sense.
2019-05-15 moved SPI interface to SERCOM 0 and added configuration notes
2019-05-15 Moved around component labels for improved readability
2019-05-15 renamed heirarchal label to be consistant
2019-05-15 updating library cache after switching header symbol
2019-05-15 moving ethernet reset and interrupt to better IO pins
2019-05-15 redid top conn mezz connector ethernet pinout
2019-05-15 Routed MCU and ethernet
    Also fixed up power planes
2019-05-15 finished clock routing
2019-05-15 fixed schematic label formatting
2019-05-16 fixing schematic label position for legibility
2019-05-16 redid i2c and status connections to microprocessor
2019-05-16 almost all i2c traces routed. all status lines routed
2019-05-16 updating fpga pinout report
2019-05-16 changing pinout to make breakout easier
2019-05-17 finished routing top mezz board
2019-05-17 updated footprint cache
2019-05-17 fixed all remaining DRC issues
2019-05-17 Added dimensions
2019-05-17 something c
2019-05-17 finally adding gitignore
2019-07-04 Starting to switch to main and expansion boards.
    Creating new expansion project and renaming old main project
2019-07-04 Gone to revision 2
2019-07-06 renamed left side connnector interconnect sheet
2019-07-07 top sheet uncessary
2019-07-07 sheets renumbered due to sheet removal
2019-07-07 removed 8 codecs and support circuitry
2019-07-07 changing parts around
2019-07-10 finishing ethernet modifications, annotating and finishing footprint assignment
2019-07-10 Fixed unncessary power flag on +12V
2019-07-12 Removing extra stuff from expansion board schematic
2019-07-12 Annotating modified components
2019-07-12 Initial PCB cleanup after split
2019-07-13 Reannotating entire schematic
2019-07-13 Figured out what option to use to reannotate the schematic properly
2019-07-13 removed extra connections
2019-07-13 left side connector layout before switching up codec layout
2019-07-14 annotation of power component
2019-07-14 Reworking connector pinouts to simplify board layout of CODECs
2019-07-14 Finished layout of one connector and codec.
    Commit before replicating layout
2019-07-16 more pcb work. working on left side connector positioning
2019-07-18 starting to connect expansion connector
2019-07-18 More work on expansion connector pinout connections
2019-07-19 positioned all codec-connector pairs and routed most clk and data lines
2019-07-23 changing jst footprints to use custom one with 3d models
2019-07-24 Added 3d models for diodes and Enpirion chip
2019-07-27 removed extra schematic sheet reference lines
2019-08-03 fixing AR Paths in places they don't need to be
2019-08-03 annotation changes on hierarchal sheets
2019-08-03 more anotation changes
2019-08-03 moving power input to power sheet where it should have been all along
2019-08-03 migrating right-conn changes from expansion to main
2019-08-10 left conn expansion to main rework
2019-08-10 Reannotate main schematic and pcb after expansion transition
2019-08-10 testing migration of device connectors and ESD diodes into conn.sch
    This means that I can't have the values of the connectors be the device number but hopefully it will allow me to utilize the schematic duplication features with the connectors and diodes
2019-08-10 finished layout of one conn.sch and put other codecs in place
    before using duplicate layout tool
2019-08-11 Changing FPGA pinouts again
2019-08-13 imported all schematic changes, and finished all codec - fpga routing
2019-08-14 Working on power layout for FPGA
2019-08-14 pcb updates after swapping 100nF caps
2019-08-14 some more work on power distro layout for FPGA
2019-08-15 finished FPGA power layout
    (for now)
2019-08-17 swapped around a few more pins to make layout nicer
2019-08-17 added MCU pin mux table to README
2019-08-17 starting to move clock generation and ethernet interface
2019-08-18 changed default silkscreen text size
2019-08-18 Finished ethernet layout
2019-08-18 finished all clock distribution
2019-08-18 Updated power input connector away from switchcraft barrel jack
2019-08-18 Updated power input connector
2019-08-18 mostly reworked power planes
2019-08-18 removing extraneous capacitor
2019-08-18 adding jumper to 3V3 trace
2019-08-18 revert commits adding power jumper
2019-08-18 Revert "revert commits adding power jumper"
    This reverts commit d4a96f1cacba311773a14178bcc1bf406318d366.
2019-08-18 Revert "adding jumper to 3V3 trace"
    This reverts commit 1cf6846782299e57bc90dd933044ffc431785827.
2019-08-20 finished routing resets 0-3
2019-08-20 finished routing reset traces
2019-08-21 act and link led traces routed
2019-08-25 Fixed all DRC errors. Now making the 3d model pretty :smile:
2019-08-25 Updated footprints in order to add 3d models
2019-08-28 Cleaning up silkscreen
    Hid all passive reference designators on silkscreen and added better connector labels
    based on http://blog.optimumdesign.com/toward-a-more-rational-silkscreen
2019-08-31 Updated annotation, since it seems to have gotten out of sync
2019-09-01 Some minor fixes
    - swapped 5Ω resistors to 4.99Ω resistors so I could actually buy them
    - swapped power switch connector over to a JST PH connector like the rest of the connectors.
2019-09-02 More minor changes
    fixing part numbers and adding more notes
